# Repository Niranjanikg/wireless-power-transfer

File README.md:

View this project on [CADLAB.io](https://cadlab.io/project/29142). 

# wireless-power-transfer

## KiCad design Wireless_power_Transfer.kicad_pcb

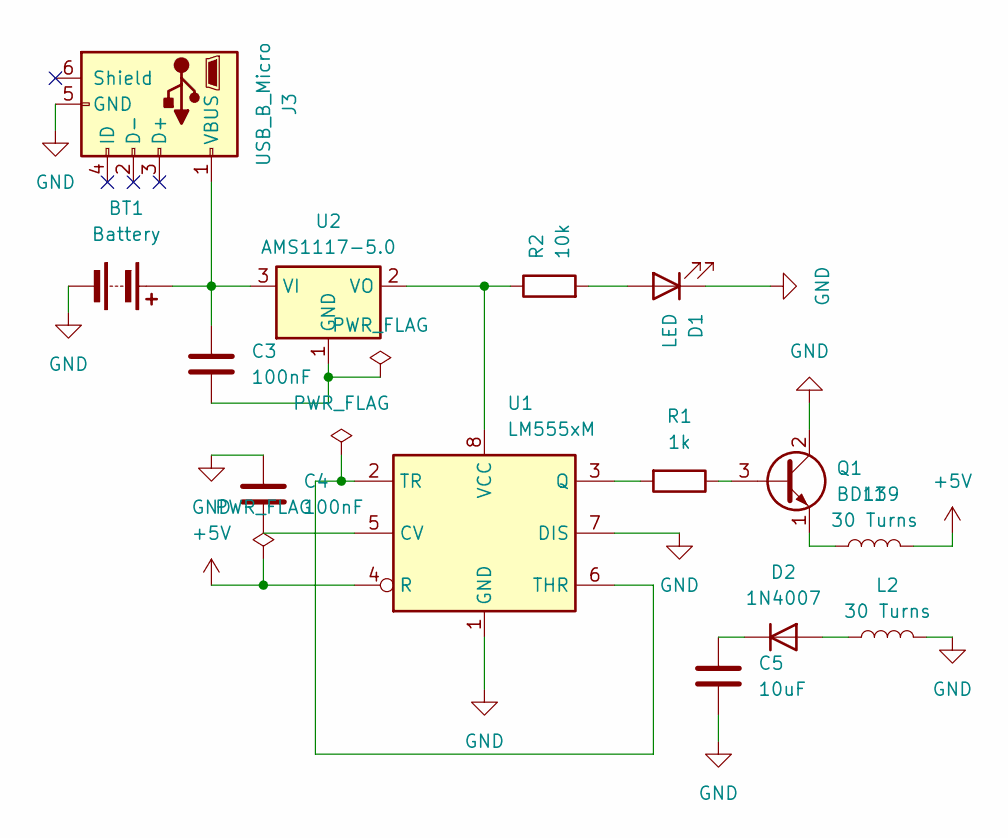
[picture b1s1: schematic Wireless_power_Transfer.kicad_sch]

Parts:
BT1: Battery; BatteryHolder_Keystone_500
C3, C4: 100nF; C_Trimmer_Murata_TZW4
C5: 10uF; C_Trimmer_Murata_TZW4
D1: LED; LED_D3.0mm_Horizontal_O1.27mm_Z2.0mm_Clear
D2: 1N4007; D_DO-41_SOD81_P10.16mm_Horizontal
J3: USB_B_Micro; USB_Micro-B_Molex-105133-0031
L1, L2: 30 Turns; Wireless_Coil_30Turns
Q1: BD139; TO-126-3_Vertical
R1: 1k; R_2512_6332Metric
R2: 10k; R_2512_6332Metric
U1: LM555xM; SOIC-8_3.9x4.9mm_P1.27mm
U2: AMS1117-5.0; SOT-223-3_TabPin2

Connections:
+5V: L1.2, U1.4 (R)
GND: BT1.2 (-), C4.1, C5.2, D1.1 (K), J3.5 (GND), L2.2, Q1.2 (C), U1.1 (GND), U1.7 (DIS)
unnamed: BT1.1 (+), C3.1, J3.1 (VBUS), U2.3 (VI)
unnamed: D1.2 (A), R2.2
unnamed: D2.2 (A), L2.1
unnamed: C5.1, D2.1 (K)
unnamed: Q1.3 (B), R1.1
unnamed: L1.1, Q1.1 (E)
unnamed: C4.2, U1.5 (CV)
unnamed: R1.2, U1.3 (Q)
unnamed: U1.2 (TR), U1.6 (THR)
unnamed: R2.1, U1.8 (VCC), U2.2 (VO)
unnamed: C3.2, U2.1 (GND)

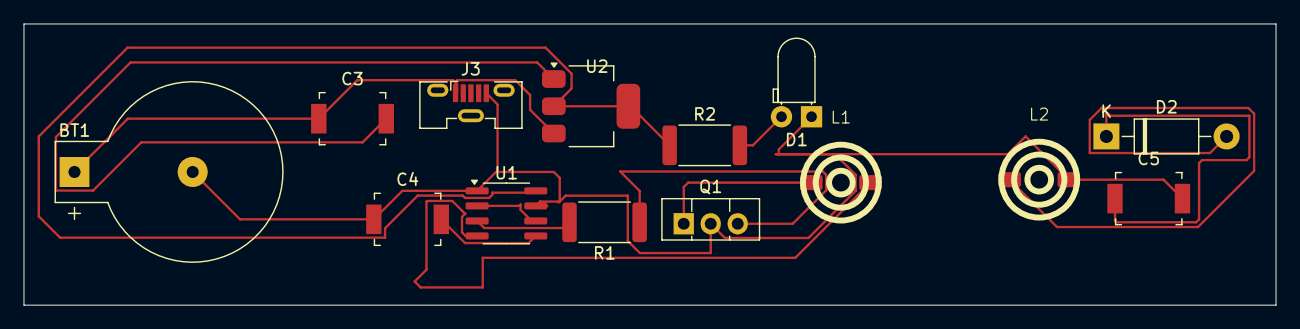
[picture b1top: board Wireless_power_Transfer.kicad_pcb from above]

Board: 2 copper layers, 105.8 x 23.8 mm, 14 parts (0 on the bottom side), 13 nets.

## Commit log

2025-04-02 Kicad project
2025-04-02 Backlink to CADLAB.io has been added.
2025-04-02 updated schematic
